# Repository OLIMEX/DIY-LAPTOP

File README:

<br>

# TERES-I Laptop

<br><br>

## Overview

TERES-I is a Do-It-Yourself (DIY) Free/Open Source Hardware ([FOSH](https://wikipedia.org/wiki/Open-source_hardware)) and Software ([FOSS](https://wikipedia.org/wiki/Free_and_open-source_software)) laptop design leveraging ARM64 and x86 processors.
DIY kits are ready-to-assemble using the [instructions provided](doc/web/hw_assembly.md) and may be purchased [here](https://www.olimex.com/Products/DIY-Laptop/KITS).

* [What is TERES-I?](doc/web/intro_what-is-teres-i.md)
* [Where does the name TERES come from?](doc/web/intro_name-origin.md)
* [What makes this laptop so different?](doc/web/intro_what-is-unique.md)
* [Why does open-source matter so much?](doc/web/intro_importance-of-open-source.md)
* [Where are the open-source materials?](doc/web/intro_sources.md)

## Assembling your TERES-I

* [What do you get in the package?](doc/web/hw_in-the-box.md)
* [Assembling your TERES-I laptop](doc/web/hw_assembly.md)

## Hardware

* [TERES-A64-WHITE](https://www.olimex.com/Products/DIY-Laptop/KITS/TERES-A64-WHITE/open-source-hardware)
* [TERES-A64-BLACK](https://www.olimex.com/Products/DIY-Laptop/KITS/TERES-A64-BLACK/open-source-hardware)
* [Spare parts](https://www.olimex.com/Products/DIY-Laptop/SPARE-PARTS/)

## Software

TERES-I was designed to run on Linux distributions, but may also run Android and Windows operating systems.

* [Installing a fresh official image to TERES-I](doc/web/sw_fresh-os.md)
* [Updating an image](doc/web/sw_updating-os.md)
* [Building an image](SOFTWARE/A64-TERES/scripts/README.md)

## Other resources

* [FAQ](doc/web/res_faq.md)
* [Troubleshooting](doc/web/res_troubleshooting.md)
* [Download manuals](doc/manuals)
* [What's next?](doc/web/res_next-steps.md)
* [Community Links](doc/web/res_community.md)

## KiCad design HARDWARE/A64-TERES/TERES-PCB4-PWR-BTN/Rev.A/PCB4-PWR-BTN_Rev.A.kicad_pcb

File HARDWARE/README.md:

# Hardware

## Overview

All hardware schematics and board files are designed using [KiCad](http://kicad-pcb.org) open-source CAD software.

> KiCad is free software. KiCad is made available under the [GNU General Public License (GPL) version 3](https://www.gnu.org/licenses/gpl-3.0.en.html) or greater.

You may download KiCad and open for reviewing or editing each of the PCB files.
The schematics are also available as PDF files for easier viewing and/or printing.

**NOTE**: Please use the latest KiCad nightly development build, as the latest stable build may not have all required features.

## Introduction to the hardware of TERES-I

TERES-I internal electronics consists of the folowing boards:

### Main board ([PCB1-A64-MAIN](A64-TERES/TERES-PCB1-A64-MAIN))

The main board (**PCB1-A64-MAIN**) is comprised of:

* A64 processor
* RAM and flash NAND memories
* Power management unit
* LCD converter
* Connectors to different interfaces
* and others

Alternative main board processors and memory configuration options will be available in the future.
These should be compatible with all other existing boards.
Subsequent revisions are expected to have increased processing speed and improved memory performance.

### Keyboard controller ([TERES-PCB5-KEYBOARD](A64-TERES/TERES-PCB5-KEYBOARD))

The **KEYBOARD controller** board (**TERES-PCB5-KEYBOARD**) is responsible for handling the keyboard and touch pad interfaces.
This keyboard controller board allows you to completely reprogram the keyboard mapping and response according to your own taste.

This board contains an AVR processor.
Sources, binaries and update procedures for AVR firmware are available at GitHub.
Keyboard/touch controller firmware may be updated live on the board itself.
It can also be programmed using an Arduino microcontroller.
Touch screen parameters can also be changed.

### I/O board ([TERES-PCB2-IO](A64-TERES/TERES-PCB2-IO))

The **IO** board (**TERES-PCB2-IO**) is comprised of:

- USB connector
- Headphone/debug connector
- SD card
- Speaker connector
- Microphone

### Power button ([TERES-PCB4-PWR-BTN](A64-TERES/TERES-PCB4-PWR-BTN))

The **PWR** button board (**TERES-PCB4-PWR-BTN**) handles the keys for powering on and off the laptop.

### Touch buttons ([TERES-PCB3-TOUCH-BTN](A64-TERES/TERES-PCB3-TOUCH-BTN))

The **TOUCH** buttons board (**TERES-PCB3-TOUCH-BTN**) contains two buttons for left and right mouse click emulation.

### Camera ([TERES-019-Camera](A64-TERES/TERES-019-Camera))

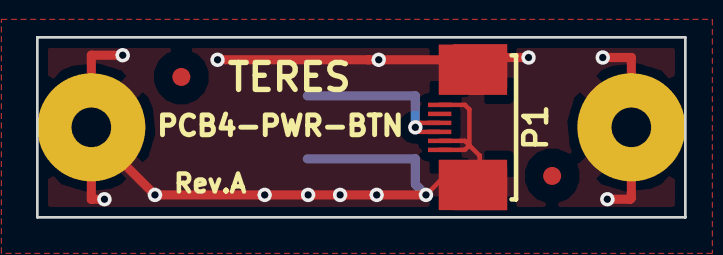
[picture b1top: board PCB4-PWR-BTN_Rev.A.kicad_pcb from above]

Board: 2 copper layers, 36.0 x 10.0 mm, 4 parts (1 on the bottom side), 2 nets.

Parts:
MountingHole: Mounting_hole_2.5mm
MountingHole#2: Mounting_hole_2.5mm
P1: WZA21-06; FLEXCON-0.5-6
SW1: SW_PUSH; tacktil_5x5_teres

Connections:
GND: P1.1, P1.2, P1.6, SW1.1
unnamed: P1.3, P1.4, SW1.2

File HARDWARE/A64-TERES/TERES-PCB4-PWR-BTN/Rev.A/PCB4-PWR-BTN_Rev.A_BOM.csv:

"Id";"Designator";"Package";"Quantity";"Designation";"Supplier and ref";
1;"P1";"FLEXCON-0.5-6";1;"WZA21-06";;;
2;"SW1";"tacktil_5x5_teres";1;"SW_PUSH";;;

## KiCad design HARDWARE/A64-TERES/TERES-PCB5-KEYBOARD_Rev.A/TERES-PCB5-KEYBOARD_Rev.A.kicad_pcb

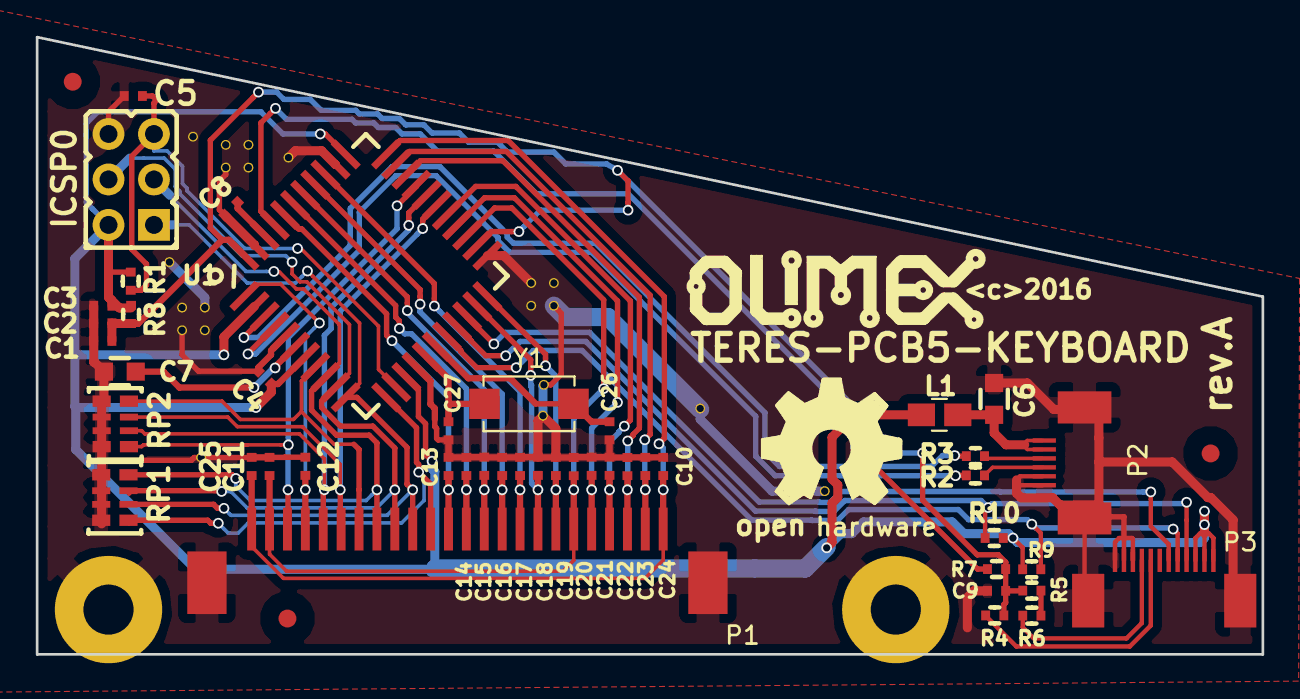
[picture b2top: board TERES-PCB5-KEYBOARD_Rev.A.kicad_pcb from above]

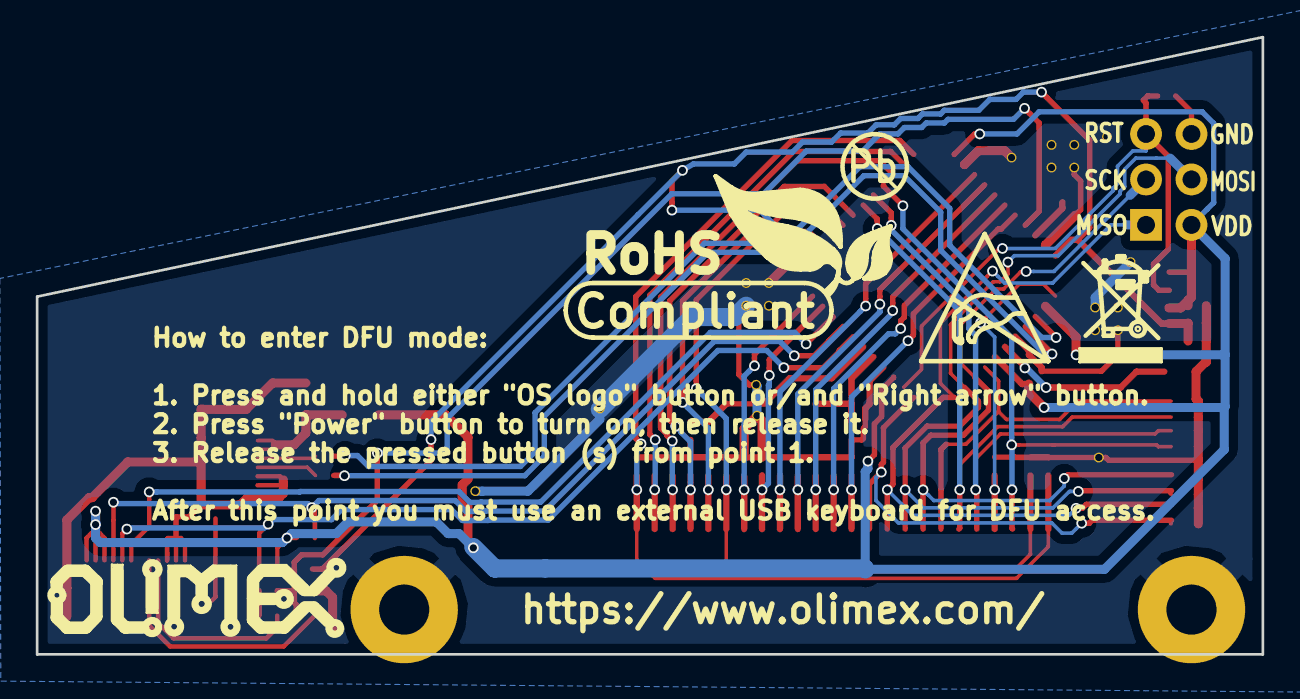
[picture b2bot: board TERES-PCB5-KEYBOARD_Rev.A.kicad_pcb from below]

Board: 2 copper layers, 68.5 x 34.5 mm, 50 parts (2 on the bottom side), 42 nets.

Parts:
C1, C2: 220nF; C0402
C3, C4, C5, C8, C9: 100nF; C0402
C6, C7: 1uF; C_0603_5MIL_DWS
C10, C11, C12, C13, C14, C15, C16, C17, C18, C19, C20, C21, C22, C23, C24, C25: 1nF; C0402
C26, C27: 22pF; C0402
ICSP0: d.n.p.(HR2x3); HN2x3
L1: FB0805; L_0805_5MIL_DWS
MountingHole: Mounting_hole_2.5mm
MountingHole#2: Mounting_hole_2.5mm
P1: CONN_01X24; FLEX-CONN-KBD-TERES-24x1
P2: CONN_01X06; FLEXCON-0.5-6
P3: CONN_01X12; FLEXCON-0.5-12
R1, R4, R5, R6, R7, R9, R10: 10K; R_0402_5MIL_DWS
R2, R3, R8: 22R; R_0402_5MIL_DWS
RP1, RP2: 4x1.5K_RA1206; R_MATRIX_4
Ref**: Val**; LOGO_ANTISTATIC_1
Ref**#2: Val**; LOGO_ROHS_1
U1: ATMEGA16U4-A; TQFP44
Y1: 16.000MHz/SMD5x3.2/12pF; Q5x3.25

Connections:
/ABUT0: C9.2, R4.1, R5.1, R7.1, U1.41
/AVDD: C1.1, C2.1, R7.2, R8.2, U1.24, U1.44
/INT: P3.7, U1.20
/KBD_X0: C21.2, P1.5, U1.26
/KBD_X1: C24.2, P1.2, U1.32
/KBD_X2: C23.2, P1.3, U1.31
/KBD_X3: C22.2, P1.4, U1.27
/KBD_X4: C18.2, P1.8, U1.21
/KBD_X5: C13.2, P1.13, U1.40
/KBD_X6: C16.2, P1.10, U1.37
/KBD_X7: C12.2, P1.21, U1.1
/KBD_X8: C14.2, P1.12, U1.39
/KBD_X9: C19.2, P1.7, U1.22
/KBD_X10: C15.2, P1.11, U1.38
/KBD_X11: C17.2, P1.9, U1.36
/KBD_X12: C10.2, C25.2, P1.1, P1.24, U1.33
/KBD_X14: C11.2, C20.2, P1.6, P1.23, U1.25
/KBD_Y0: ICSP0.4, P1.16, U1.10
/KBD_Y1: ICSP0.3, P1.17, U1.9
/KBD_Y2: P1.14, U1.12
/KBD_Y3: P1.18, U1.8
/KBD_Y4: P1.19, U1.28
/KBD_Y5: P1.20, U1.29
/KBD_Y6: P1.22, U1.30
/KBD_Y7: ICSP0.1, P1.15, U1.11
/RESET: C5.2, ICSP0.5, R1.2, U1.13
/SCL: P3.8, R9.1, U1.18
/SDA: P3.9, R10.1, U1.19
/SW_L: P3.5, R4.2
/SW_R: P3.4, R6.2
/USB_D_N: P2.4, R3.1
/USB_D_P: P2.3, R2.1
/USB_VBUS: C6.2, L1.2, P2.5, P2.6
/VDD: C3.1, C4.1, ICSP0.2, L1.1, P3.10, P3.11, P3.12, R1.1, R8.1, R9.2, R10.2, U1.2, U1.7, U1.14, U1.34
GND: C1.2, C2.2, C3.2, C4.2, C5.1, C6.1, C7.2, C8.1, C9.1, C10.1, C11.1, C12.1, C13.1, C14.1, C15.1, C16.1, C17.1, C18.1, C19.1, C20.1, C21.1, C22.1, C23.1, C24.1, C25.1, C26.1, C27.1, ICSP0.6, P1.0, P2.0, P2.1, P2.2, P3.0, P3.1, P3.2, P3.3, U1.5, U1.15, U1.23, U1.35, U1.43
unnamed: C7.1, U1.6
unnamed: C8.2, U1.42
unnamed: C26.2, U1.17, Y1.1
unnamed: C27.2, U1.16, Y1.2
unnamed: R2.2, U1.4
unnamed: R3.2, U1.3
unnamed: R5.2, R6.1

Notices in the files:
HARDWARE/A64-TERES/TERES-PCB4-PWR-BTN/Rev.A/PCB4-PWR-BTN_Rev.A.kicad_pcb:
(C) 2016
